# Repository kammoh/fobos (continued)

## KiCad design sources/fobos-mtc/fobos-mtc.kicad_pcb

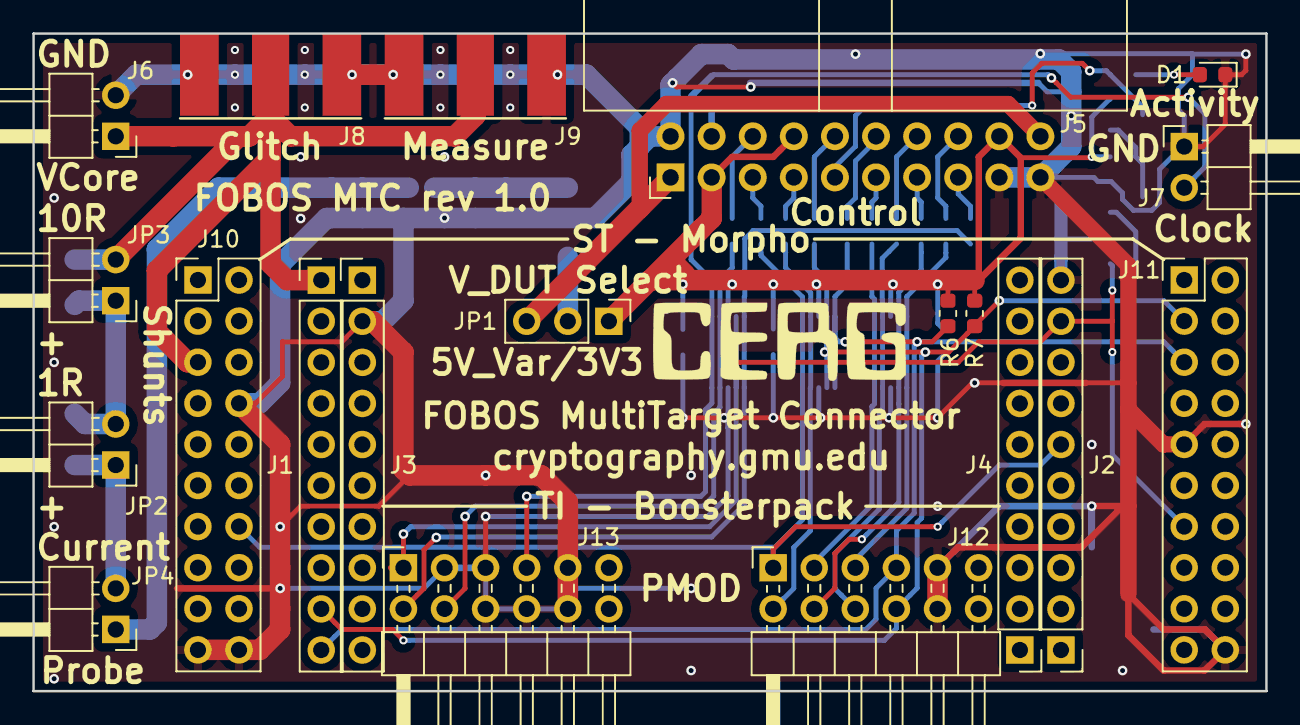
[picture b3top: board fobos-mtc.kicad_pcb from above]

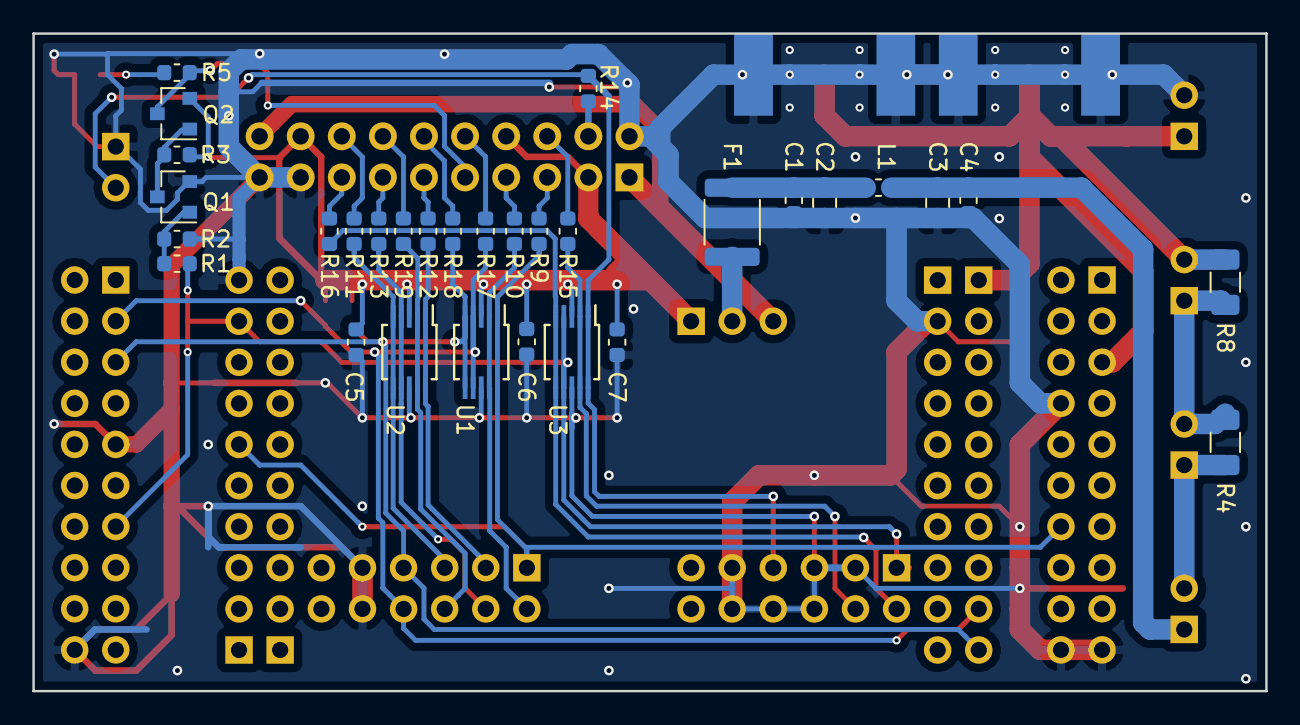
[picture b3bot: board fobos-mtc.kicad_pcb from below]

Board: 2 copper layers, 76.2 x 40.6 mm, 51 parts (31 on the bottom side), 36 nets.

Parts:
C1, C4, C5, C6, C7: 100nF; C_0603_1608Metric
C2: 10uF; C_0805_2012Metric
C3: 47uF6.3V; C_0805_2012Metric
D1: Activity; LED_0603_1608Metric
F1: MF-MSMF050-2; Fuse_1812_4532Metric
J1, J2, J3, J4: Conn_01x10; PinHeader_1x10_P2.54mm_Vertical
J5: Target; IDC-Header_2x10_P2.54mm_Horizontal
J6: Conn_01x02; PinHeader_1x02_P2.54mm_Horizontal
J7: clk; PinHeader_1x02_P2.54mm_Horizontal
J8: Glitch; SMA-JOHNSON-142-0701-801
J9: Measure; SMA-JOHNSON-142-0701-801
J10, J11: Conn_02x10_Odd_Even; PinSocket_2x10_P2.54mm_Vertical-flipped
J12, J13: Conn_02x06_Top_Bottom; PinHeader_2x06_P2.54mm_Horizontal-flipped
JP1: Source; PinHeader_1x03_P2.54mm_Vertical
JP2: Shunt1R; PinHeader_1x02_P2.54mm_Horizontal
JP3: Shunt10R; PinHeader_1x02_P2.54mm_Horizontal
JP4: CurProbe; PinHeader_1x02_P2.54mm_Horizontal
L1: 1k/500mA; L_0603_1608Metric
Q1: BSS138; SOT-23
Q2: BSS84; SOT-23
R1, R9, R10, R11, R12, R13, R14, R15, R16, R17, R18, R19: 22R; R_0603_1608Metric
R2, R3, R6, R7: 10k; R_0603_1608Metric
R4: 1R; R_1206_3216Metric
R5: 470R; R_0603_1608Metric
R8: 10R; R_1206_3216Metric
U1, U2, U3: SP3003-04ATG; MSOP-10_3x3mm_P0.5mm

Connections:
/dutconnect/CV_RST: J5.5, R9.1
/dutconnect/CW_HS1: J5.4, R14.2
/dutconnect/CW_HS2: J5.6, R15.2
/dutconnect/CW_MISO: J5.7, R10.1
/dutconnect/CW_PDIC: J5.13, R13.1
/dutconnect/CW_PDID: J5.15, R16.1
/dutconnect/CW_SCK: J5.11, R12.1
/dutconnect/CW_TARG1: J5.10, R17.2
/dutconnect/CW_TARG2: J5.12, R18.2
/dutconnect/CW_TARG3: J5.14, R19.2
/dutconnect/CW_TARG4: J5.16, R11.2
Aux: J13.7, R16.2, U3.5, U3.6
CLK_C2D: J13.8, R15.1, U3.2, U3.9
CLK_D2C: J7.2, J13.4, R14.1, U3.1, U3.10
CW_3V3: C5.1, C6.1, C7.1, J5.3, J5.8, J5.18, JP1.1, Q2.2, R3.1, R6.2, R7.2, U1.3, U2.3, U3.3
CW_5V: J5.1, J5.20, JP1.3
DIO0: J1.9, J11.3, J12.10, R7.1, R17.1, U1.4, U1.7
DIO1: J1.10, J11.5, J12.4, R6.1, R18.1, U1.5, U1.6
DIO2: J12.9, R19.1, U2.2, U2.9
DIO3: J12.3, R11.1, U2.5, U2.6
GND: C1.2, C2.2, C3.2, C4.2, C5.2, C6.2, C7.2, D1.1, J2.10, J3.2, J5.2, J5.17, J5.19, J6.2, J7.1, J8.2, J9.2, J10.8, J10.19, J10.20, J11.9, J11.20, J12.5, J12.11, J13.2, J13.3, J13.5, J13.9, J13.10, J13.11, Q1.2, R2.2, U1.8, U2.8, U3.8
IO: J12.7, R10.2, U1.2, U1.9
unnamed: C1.1, C2.1, F1.1, L1.2
unnamed: D1.2, R5.2
unnamed: F1.2, JP1.2
unnamed: JP2.1, JP4.2, R4.2
unnamed: JP2.2, JP3.1, R4.1, R8.2
unnamed: Q1.1, R1.1, R2.1
unnamed: Q1.3, Q2.1, R3.2
RST: J2.6, J10.14, J12.1, R9.2, U1.1, U1.10
Ready: J12.2, R12.2, U2.1, U2.10
TF: J5.9, Q2.3, R5.1
TFD: J2.9, J11.13, J13.1, R1.2, U3.4, U3.7
V_XBD: J1.1, J6.1, J8.1, J9.1, J10.5, JP3.2, R8.1
Valid: J12.8, R13.2, U2.4, U2.7
XBD_AVCC: C3.1, C4.1, JP4.1, L1.1

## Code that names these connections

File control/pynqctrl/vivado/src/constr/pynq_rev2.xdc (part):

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
set_property -dict {PACKAGE_PIN Y18 IOSTANDARD LVCMOS33} [get_ports { dut_rst }]; #IO_L17P_T2_34 Sch=ja_p[1]
set_property -dict {PACKAGE_PIN Y19 IOSTANDARD LVCMOS33} [get_ports do_ready]
set_property -dict {PACKAGE_PIN Y16 IOSTANDARD LVCMOS33} [get_ports {din[3]}]
#set_property -dict {PACKAGE_PIN Y17 IOSTANDARD LVCMOS33} [get_ports {iic_rtl_scl_io}]
set_property -dict {PACKAGE_PIN U18 IOSTANDARD LVCMOS33} [get_ports do_valid]
##repeated for Artix7 DUT
set_property -dict {PACKAGE_PIN U19 IOSTANDARD LVCMOS33} [get_ports {din[1]}]; #IO_L12N_T1_MRCC_34 Sch=ja_n[3] 
set_property -dict {PACKAGE_PIN W18 IOSTANDARD LVCMOS33} [get_ports {din[2]}]
set_property -dict {PACKAGE_PIN W19 IOSTANDARD LVCMOS33} [get_ports {din[0]}]

#Pmod Header JB

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set_property -dict {PACKAGE_PIN V7  IOSTANDARD LVCMOS33} [get_ports {adc[7]}];        #IO30
set_property -dict {PACKAGE_PIN V15 IOSTANDARD LVCMOS33} [get_ports {adc[8]}];        #IO4
set_property -dict {PACKAGE_PIN U8  IOSTANDARD LVCMOS33} [get_ports {adc[9]}];        #IO31
set_property -dict {PACKAGE_PIN T15 IOSTANDARD LVCMOS33} [get_ports {adc_or}];        #IO5

set_property -dict {PACKAGE_PIN U7  IOSTANDARD LVCMOS33} [get_ports {adc_clk}];       #IO29
set_property drive 16 [get_ports adc_clk]

set_property -dict {PACKAGE_PIN W15 IOSTANDARD LVCMOS33} [get_ports {adc_gain_mode}]; #spi-miso
set_property -dict {PACKAGE_PIN H15 IOSTANDARD LVCMOS33} [get_ports {adc_gain}];      #spi-sck

## Glitch Circuit
set_property -dict {PACKAGE_PIN T12 IOSTANDARD LVCMOS33} [get_ports {glitch}];        #spi-mosi
set_property -dict {PACKAGE_PIN F16 IOSTANDARD LVCMOS33} [get_ports {glitch_lp}];     #spi-ss

## Power
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set_property -dict {PACKAGE_PIN Y13 IOSTANDARD LVCMOS33} [get_ports power_en];        #IOA

## TARGET Header
set_property -dict {PACKAGE_PIN P15 IOSTANDARD LVCMOS33} [get_ports {fc_rst}];        #i2c-sda

set_property -dict {PACKAGE_PIN V18 IOSTANDARD LVCMOS33} [get_ports {fc_dio[0]}];     #IO9
set_property -dict {PACKAGE_PIN V17 IOSTANDARD LVCMOS33} [get_ports {fc_dio[1]}];     #IO8
set_property -dict {PACKAGE_PIN U17 IOSTANDARD LVCMOS33} [get_ports {fc_dio[2]}];     #IO7
set_property -dict {PACKAGE_PIN R16 IOSTANDARD LVCMOS33} [get_ports {fc_dio[3]}];     #IO6

set_property -dict {PACKAGE_PIN W10 IOSTANDARD LVCMOS33} [get_ports {fc2d_hs}];       #IO34 
set_property -dict {PACKAGE_PIN V10 IOSTANDARD LVCMOS33} [get_ports {fd2c_hs}];       #IO33
set_property -dict {PACKAGE_PIN Y6  IOSTANDARD LVCMOS33} [get_ports {fc_io}];         #IO36


set_property -dict {PACKAGE_PIN V8  IOSTANDARD LVCMOS33} [get_ports {fc_prog}];       #IO32
set_property -dict {PACKAGE_PIN W6  IOSTANDARD LVCMOS33} [get_ports {fd_tf}];         #IO35

set_property -dict {PACKAGE_PIN Y7  IOSTANDARD LVCMOS33} [get_ports {fc2d_clk}];      #IO37
set_property -dict {PACKAGE_PIN Y9  IOSTANDARD LVCMOS33} [get_ports {fd2c_clk}];      #IO41

## TRIGGER
set_property -dict {PACKAGE_PIN P16 IOSTANDARD LVCMOS33} [get_ports {trigger}];       #i2c-scl

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
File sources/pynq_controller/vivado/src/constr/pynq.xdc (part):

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
set_property -dict {PACKAGE_PIN Y18 IOSTANDARD LVCMOS33} [get_ports { dut_rst }]; #IO_L17P_T2_34 Sch=ja_p[1]
set_property -dict {PACKAGE_PIN Y19 IOSTANDARD LVCMOS33} [get_ports do_ready]
set_property -dict {PACKAGE_PIN Y16 IOSTANDARD LVCMOS33} [get_ports {din[3]}]
set_property -dict {PACKAGE_PIN Y17 IOSTANDARD LVCMOS33} [get_ports {iic_rtl_scl_io}]
set_property -dict {PACKAGE_PIN U18 IOSTANDARD LVCMOS33} [get_ports do_valid]
##repeated for Artix7 DUT
set_property -dict {PACKAGE_PIN U19 IOSTANDARD LVCMOS33} [get_ports {din[1]}]; #IO_L12N_T1_MRCC_34 Sch=ja_n[3] 
set_property -dict {PACKAGE_PIN W18 IOSTANDARD LVCMOS33} [get_ports {din[2]}]
set_property -dict {PACKAGE_PIN W19 IOSTANDARD LVCMOS33} [get_ports {din[0]}]

#Pmod Header JB

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set_property -dict {PACKAGE_PIN C20 IOSTANDARD LVCMOS33} [get_ports {gain_0[0]}]
set_property -dict {PACKAGE_PIN F20 IOSTANDARD LVCMOS33} [get_ports {gain_1[1]}]
set_property -dict {PACKAGE_PIN F19 IOSTANDARD LVCMOS33} [get_ports {gain_1[0]}]
set_property -dict {PACKAGE_PIN A20 IOSTANDARD LVCMOS33} [get_ports trigger]
#set_property -dict { PACKAGE_PIN B19   IOSTANDARD LVCMOS33 } [get_ports { ck_io[25] }]; #IO_L2P_T0_AD8P_35 Sch=ad_p[8]

##ChipKit Digital I/O High
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set_property -dict { PACKAGE_PIN U5    IOSTANDARD LVCMOS33 } [get_ports { io }]; #IO_L19N_T3_VREF_13 Sch=ck_io[26]
#set_property -dict { PACKAGE_PIN V5    IOSTANDARD LVCMOS33 } [get_ports { d_tf }]; #IO_L6N_T0_VREF_13 Sch=ck_io[27]
set_property -dict { PACKAGE_PIN V6    IOSTANDARD LVCMOS33 } [get_ports { handshake_c2d }]; #IO_L22P_T3_13 Sch=ck_io[28]
#set_property -dict { PACKAGE_PIN U7    IOSTANDARD LVCMOS33 } [get_ports { clk_d2c }]; #IO_L11P_T1_SRCC_13 Sch=ck_io[29]
set_property -dict { PACKAGE_PIN V7    IOSTANDARD LVCMOS33 } [get_ports { dio[3] }]; #IO_L11N_T1_SRCC_13 Sch=ck_io[30]
set_property -dict { PACKAGE_PIN U8    IOSTANDARD LVCMOS33 } [get_ports { adc[0] }]; #IO_L17N_T2_13 Sch=ck_io[31]
set_property -dict { PACKAGE_PIN V8    IOSTANDARD LVCMOS33 } [get_ports { adc[2] }]; #IO_L15P_T2_DQS_13 Sch=ck_io[32]
set_property -dict { PACKAGE_PIN V10   IOSTANDARD LVCMOS33 } [get_ports { adc[4] }]; #IO_L21N_T3_DQS_13 Sch=ck_io[33]
set_property -dict { PACKAGE_PIN W10   IOSTANDARD LVCMOS33 } [get_ports { adc[6] }]; #IO_L16P_T2_13 Sch=ck_io[34]
set_property -dict { PACKAGE_PIN W6    IOSTANDARD LVCMOS33 } [get_ports { adc[8] }]; #IO_L22N_T3_13 Sch=ck_io[35]
#set_property -dict { PACKAGE_PIN Y6    IOSTANDARD LVCMOS33 } [get_ports { adc_or }]; #IO_L13N_T2_MRCC_13 Sch=ck_io[36]
set_property -dict { PACKAGE_PIN Y7    IOSTANDARD LVCMOS33 } [get_ports { clk_c2d }]; #IO_L13P_T2_MRCC_13 Sch=ck_io[37]
set_property -dict {PACKAGE_PIN W8 IOSTANDARD LVCMOS33} [get_ports {power[1]}]
set_property -dict {PACKAGE_PIN Y8 IOSTANDARD LVCMOS33} [get_ports {power[3]}]
set_property -dict {PACKAGE_PIN W9 IOSTANDARD LVCMOS33} [get_ports {power[5]}]
set_property -dict { PACKAGE_PIN Y9    IOSTANDARD LVCMOS33 } [get_ports { adc_clk }]; #IO_L14P_T2_SRCC_13 Sch=ck_io[41]
set_property drive 16 [get_ports adc_clk]
set_property -dict {PACKAGE_PIN Y13 IOSTANDARD LVCMOS33} [get_ports power_ok]

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
#set_property -dict { PACKAGE_PIN W15   IOSTANDARD LVCMOS33 } [get_ports { glitch_hp }]; #IO_L10N_T1_34 Sch=ck_miso
set_property -dict { PACKAGE_PIN T12   IOSTANDARD LVCMOS33 } [get_ports { adc_gain }]; #IO_L2P_T0_34 Sch=ck_mosi
#set_property -dict { PACKAGE_PIN H15   IOSTANDARD LVCMOS33 } [get_ports { glitch }]; #IO_L19P_T3_35 Sch=ck_sck
set_property -dict { PACKAGE_PIN F16   IOSTANDARD LVCMOS33 } [get_ports { adc_gain_mode }]; #IO_L6P_T0_35 Sch=ck_ss

## ChipKit I2C
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
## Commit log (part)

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2019-02-07 added IOs for powermanager
2019-02-13 Added dutcomm and dutcontroller IPs and tested communication with internal DUT successfully. Python code in Jupyter note book format is added. Changed dutcomm to assert tlast.
    new file: ../../../python3/code.ipynb
    modified: ../../Makefile
    modified: ../../build_proj.tcl
    new file: ../dut_aes/FOBOS_DUT.vhd
    new file: ../dut_aes/aes_axi.vhd
    new file: ../dut_aes/aes_non_pipe.vhd
2019-02-20 Powermanager IP added
2019-02-28 added FPGA pinouts and fixed 2 bugs
2019-03-01 started layout of mtc
2019-03-01 still working on layout of MTC
2019-03-04 added more stuff for MTC
2019-03-14 added all FOBOS shield pins to xdc
2019-03-20 Addedd OpenADC Interface IP to controller hardware
2019-03-22 Corrected block_design to use PS clock.
2019-03-24 FOBOS Roadmap slides added
2019-03-25 updates to presentation
2019-03-25 power module code
2019-03-26 removed FOBOS roadmap persentation, now FOBOS speed analysis
2019-03-26 RSA and AES computation speed correction
2019-03-26 send to Riscure
2019-03-29 Cleaned up capture code
2019-04-08 Created analyzer/cpa.py module
2019-04-09 Added a test-bench for dutcomm IP
2019-04-11 Added support for selecting legacy interface vs new bi-directional interface
2019-04-13 Tested half-duplex interface successfully
2019-04-16 Nexys4 DUT UCF fixed, uses PMODs A and B
2019-04-16 We can now switch between 4bit and 8bit DUT interface.
2019-04-23 Started working on CPA online function
2019-04-24 Changed plaintext and cihpertext file format for ease of read in the analysis module
2019-04-24 Added online t-test
2019-04-30 Tested running Kyber
2019-05-03 Ran online t-test on Kyber
2019-05-07 forgot to commit before
2019-05-07 moved fobos-ti-launchpad stuff to fobos-mtc
2019-05-12 Corrected buffer sizes in ctrl.c
2019-05-14 Fixed isses related to testvector buffer/fifo sizes
2019-05-21 Added suport for Picoscope 5000 oscilloscope
2019-05-22 fixed ciphertext formatting
2019-05-23 Fixed isses with max possible sampling rate and data buffer allocation
2019-05-23 Improved MTD grahp plot
2019-05-30 Added scripts to program DUTs
2019-06-07 Updated t-test and profiler tools
2019-06-07 Update DUTcomm IP. Re-organized directory structure.
2019-06-10 modified dutcomm IP testbench
2019-06-10 added DUTController IP documentation
2019-06-12 Added dynamic clock configuration for Basys3 controller
2019-06-15 Added a warning on soc_dut dut.c. Modified zybo.xdc to match the controller
2019-06-21 Pynqctrl: Reduced default DUT frequency from 100MHz to 5Mhz. It seems 100MHz causes errors
2019-06-21 Corrected constrain files to be compatible with Artix7-CW305 board pins
2019-07-18 Fixed a typo in a function call in picoscope.py
2019-07-19 Re-organized software directory. Modified analysis software.
2019-08-02 error in fig
2019-08-13 re-organized directory structure
2019-08-20 Added test mode. Fixed issues with timout and reset features.
2019-08-27 Removed test-vector and result divisibility by 4 restriction.
2019-08-30 Added comments and cleaned up files
2019-09-04 Fixed file format.
2019-09-24 modified attack_with_cpa.py
2019-10-08 Added new doc directory for Shpinx doc
2019-10-10 Fixed an issue with ctrl.c that prevented dutcomm from working on non-test mode.
2019-10-10 Added python packages requirements file
2019-10-25 Fobos 3 DUT power
2019-11-02 modified software/fobos/__init__.py to add OK attribute
2019-11-02 Fixed blockCipherTVGen.py and moved it to software/tvgen
2019-11-02 Updated documentation
2019-11-03 Moved dut files to capture/dut
2019-11-03 Update documentation
2019-11-05 Added cpaExample.py and chi-squared test script
2019-11-07 Fixed documentation issue that prevented build
2019-11-13 added a note
2019-11-19 modified sphinx latex output
2019-11-19 not much
2019-11-21 trying new template
2019-11-26 added comments and made some fixes
2019-11-26 Updated presentation
2019-12-04 Added Reconfi-19 presentation
2019-12-09 typos corrected
2019-12-10 back to read the docs style
2019-12-10 removed notices for Bakry
2019-12-11 added reconfig presentation
2019-12-11 minor update in documentation
2019-12-20 some modifications to the shield
2019-12-23 Upgraded to Vivado 2019.1
2020-01-16 Added Reconfig-19 demo to docs
2020-01-28 Added power glitch feature
2020-01-29 forgot
2020-01-29 Updated setup documentation to install needed pakages for Ubuntu 18.04
2020-02-07 Created t-test4.py. This file uses memory-mapped numpy arrays to keep traces in the disk to save memory
2020-02-25 fixed issues with the power glicth functionality
2020-02-26 work in progress
2020-02-28 started open ADC layout
2020-03-10 FOBOS3 can now run on PC with TCP connection to PYNQ (partial)
2020-03-10 Saved old work and added pynqserver feature
2020-03-15 Added Jupyter installation notes
2020-03-30 Improved pynqserver and watchdog
2020-03-31 Added client watchdog. fixed issues with pynq ctrl
2020-03-31 added ece476 CPA lab
2020-04-07 Changed directory naming in projmgr to attempt-xx, analysis-xx
2020-04-07 Enlarged output plots
2020-04-07 added code to save config in capture dir
2020-04-12 Cleared ADC gain on disconnect
2020-04-13 fixed top-n key report and imporoved graphs
2020-04-13 fixed adc gain limit message
2020-04-13 updated cpa lab docs
2020-04-15 improved powermodel calculations output meesages
2020-04-16 cpa graphs are now configurable
2020-04-16 added power model display function
2020-04-22 added 3d model of heat sink
2020-05-27 still working on new layout
2020-06-10 added README.md
2020-06-30 Fixed an issue with the t-test4.py script
2020-07-07 Fixed timeout issue in pynqserver.py
2020-07-16 Cleaned up FOBOS directory structure. Now it matches the README
2020-07-16 added resources for DUT design
2020-07-21 Update README.md, moved FOBOS DUT Development from Readme.md to Wiki
2020-07-27 moved 3d models to subdirectory, updated paths
2020-07-28 more pcb library cleanup
2020-07-30 started artix7 dut development
2020-08-01 artix 7 dut PCB work
2020-10-30 updated 3d model path of sma connector
2020-11-24 moving ADC
2020-11-25 Adding LTC3633 power chip to CERG lib
2020-12-15 Removed LTC3633 dual output power switcher IC Added LTC3569 triple output power switcher IC
2020-12-16 more changes to FOBOS Shield rev2
2020-12-21 Added PGOOD LED and NFET Connected INA225 to Current shunt resistor
2020-12-29 renamed 20-pin connector signals
2020-12-30 completed change of signal names on target connector
2021-01-11 FOBOS Shield rev2 ready for review
2021-01-13 Updating cerg.lib
2021-01-22 starting to fill areas
2021-01-23 ready for review
2021-01-24 disconnected XADC ground from GND
2021-02-05 Schematic is 99% complete, getting started on layout
2021-02-11 added SMA for input from INA225 on DUT
2021-02-15 Preliminary placement underway Made a copy of cerg 3d model within Artix 7 dut project to resolve nagging library path issue
2021-03-04 labs are not working with foboslib
2021-03-04 added file to gitignore
2021-03-08 small fixed to foboslib, not done yet
2021-03-19 bugfixes in foboslib
2021-03-23 Completed layout of the Artix 7 DUT Board
2021-03-25 added xdc files for CW305 20-pin connector
2021-04-01 added cw305 dut programming feature
2021-04-02 fixed an issue with fobos fpga wrapper that caused invalid data to be fed to crypto
2021-04-04 added a function to calculate TVLA from files
2021-04-09 cleanup of fobos software and inclusion of new sca labs
2021-04-18 Added external 5V connector Added shunt for FC3v3 and 3V3 Added silkscreen which clarifies switch functionality Thickened 5 mil traces to 7 mil where feasible Moved Vcore amplifier closer to Vcore pa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
2021-05-28 Renamed /dut-artix7-a12t to /dut-artix7-a12t-csg325 Added new directory dut-artix7-a12t-cpg238/ - U1 ARTIX 7 has been swapped for CPG238 package
2021-05-30 added cerg lib to project
2021-05-31 Added 3d model for CPG238 part Wiped out old traces and power pours
2021-06-01 Connected the fixed signals to the FPGA, flexible IO are left unconnected Added 0.1 ohm resistors to the 1V8 and 3V3 power rails, added test points which allow for easy measurement Updated ARTIX7-A12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
2021-06-06 Added SMA-JOHNSON-142-0701-201 Vertical SMA footprint to CERG lib, added this footprint to the Vcore measurement Re-positioned Power circuitry to the top right quadrant Re-positioned FOBOS connector 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
2021-06-07 few layout alignments incl space around FPGA
2021-06-08 discussion with Eddie
2021-06-08 fixed PMOD
2021-06-10 added protection for PMOD
2021-06-11 everything placed on top except decoupling caps
2021-06-22 genrated bd_tcl with vivado 2020.2
2021-06-24 Updated parts on PCB bottom side and fixed U7-U5 mixup on Silkscreen
2021-06-29 vivado 2002.2 now default
2021-06-30 new powermanager IP created and sources copied
2021-07-01 updated powermanager and pynq top level, added xdc for shield rev2
2021-07-07 updated FPGA pins and added XADC channels to schematic
2021-07-10 powermanager voltage setting and reading fixed
2021-07-31 added still incomplete power.py to foboslib and nexys4dut.py
2021-08-04 mixup of gain bits corrected
2021-08-04 checked current measurement commands in power.py
2021-08-05 Makfile and synthesis script fixed
2021-08-06 power.py ready for testing. Still missing callibration
2021-08-07 added function to check ADC overrange bit of openadc
2021-08-16 Continued to work on dut-artix7-a12t.kicad_pcb layout
2021-11-03 DUT controller can now hangle CW305
2021-11-13 few updates
2021-11-15 fixing buld tcl script
2021-11-16 updated pynq build readme and basic capture jupyter notebook
2021-11-19 added UART to PL and target switcher to dutcom
2022-01-24 All signals routed, need to route power
2022-02-04 Poured copper planes for L2 Added second 3 mil trace to Pad V12
2022-02-05 Made VCCINT one continuous plane 3V3 plane now has a small plane on the bottom layer as a result of giving up L3 room for VCCINT plane VCCINT measurement point move from VIA near BGA pad G10 to JP5P1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
2022-02-06 Fixed unconnected trace DRC error Moved position of top silkscreen designators ti fix overlap issues
2022-02-21 fobos 3 remote figure start
2022-02-23 added more figures for GLSVLSI paper
2022-02-25 Added 3D models for U8 and C1
2022-03-09 Moved PCB so that it fits inside of title block Created BOM which matches the rev 1 design Generated pick and place data, assembly drawings
2022-03-16 tiny change to pynq capture notebook
2022-03-22 added updated power notebook
2022-04-05 capture notebook with new paths
2022-04-20 Working setup for fobos shield v1.0. Added documentation for setting up Pynq ctrl with CW305.
2022-04-29 fixed a bug that causes pynq to reuse old data in the case testvector is empty (when dinFile finished)
2022-05-02 Initial commit of Cyclone 10 dut project. Layout is still underway
2022-05-02 Captured BOM changes in BOM Changes.txt Created dut-artix7-a12t-schematic.pdf
2022-05-04 Changed BGA pad diameter from 0.45mm to 0.38mm Changed BGA vias from 8/16mil to 10/18mil
2022-05-15 Updated jtag connector to match terasic usb blaster Connected SPI Flash Layout is in work
2022-05-27 fixed foboslib link on pynq
2022-05-28 fixed typo in fobosctrl, no sudo for nexys4 programing
2022-05-28 aes bit files
2022-05-31 sudo permissions fixed
2022-06-01 removed docs/labs and fixed typos in install-pynq.sh
2022-06-05 Added python_conf support, corrected several typos in powermanager calls in pynqserver
2022-06-08 dut_working now working, removed ip_repo_old
2022-06-08 added powerManager and dut_working functions to pynqctrl.py
2022-06-09 adapting basys3ctrl to python3
2022-06-15 basys3 setup ready for review
2022-06-17 more documentation
2022-06-19 trying to integrate autodoc into our sphinx documentation
2022-06-21 added dosumentation
2022-06-22 updated fpga_wrapper
2022-06-24 fixed bug in projmgr and cleaned up capture_adc
2022-06-25 added Nexys4 constraint files
2022-07-29 added BOM to artix-7 target board
2022-08-14 transitioned artix-7 dut to Kikad 6
2022-09-02 added power calibration script
2022-09-09 remove symlink
2022-09-11 updated power calibration and correct register access error in power.py
2022-09-14 dut: asym_fifo with BRAM
2022-09-16 rename uut->LWC_INST
2022-09-16 LWC as xeda dependency (requires latest xeda)
2022-09-16 cleanup
2022-09-27 full compatibility with VHDL 1993
